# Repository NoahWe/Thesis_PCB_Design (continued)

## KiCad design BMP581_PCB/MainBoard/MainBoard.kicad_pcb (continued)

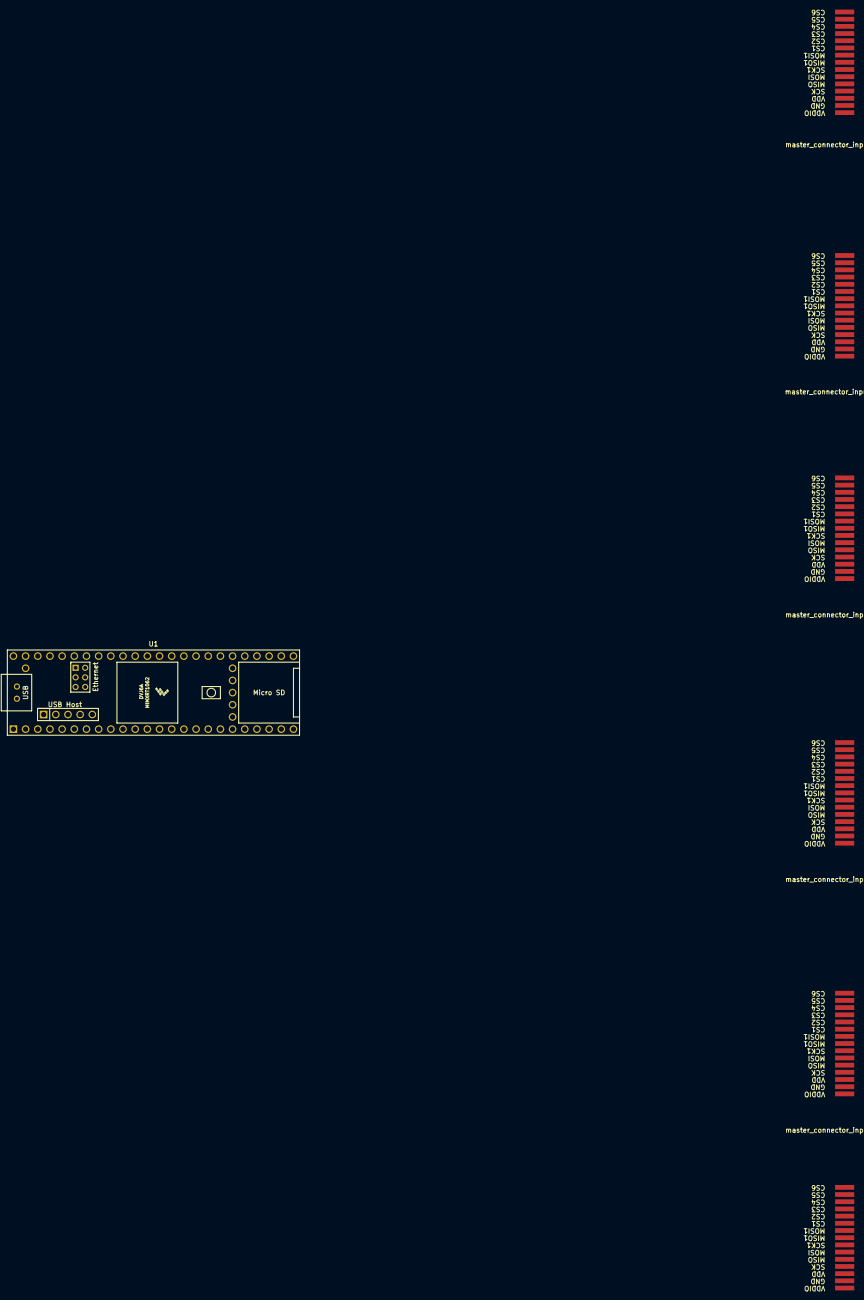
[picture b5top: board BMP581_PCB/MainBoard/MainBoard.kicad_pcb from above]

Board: 2 copper layers, 13 parts (0 on the bottom side), 42 nets.

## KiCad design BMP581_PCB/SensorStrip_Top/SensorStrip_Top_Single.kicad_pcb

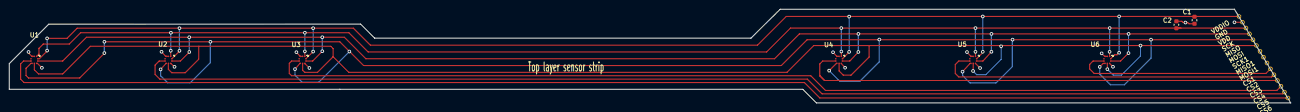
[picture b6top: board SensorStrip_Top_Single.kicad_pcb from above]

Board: 2 copper layers, 283.0 x 20.7 mm, 9 parts (0 on the bottom side), 12 nets.

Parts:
C1, C2: 470nF; C_0603_1608Metric
TopConnector1: std_master_output; Strip_pins_top
U1, U2, U3, U4, U5, U6: BMP581_Landing_Pattern

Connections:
GND: C1.1, C2.1, TopConnector1.2 (GND), U1.3 (GND), U1.8 (GND), U1.9 (GND), U2.3 (GND), U2.8 (GND), U2.9 (GND), U3.3 (GND), U3.8 (GND), U3.9 (GND), U4.3 (GND), U4.8 (GND), U4.9 (GND), U5.3 (GND), U5.8 (GND), U5.9 (GND), U6.3 (GND), U6.8 (GND), U6.9 (GND)
unnamed: TopConnector1.10 (CS1), U6.6 (CSB)
unnamed: TopConnector1.11 (CS2), U5.6 (CSB)
unnamed: TopConnector1.12 (CS3), U4.6 (CSB)
unnamed: TopConnector1.13 (CS4), U3.6 (CSB)
unnamed: TopConnector1.14 (CS5), U2.6 (CSB)
unnamed: TopConnector1.15 (CS6), U1.6 (CSB)
unnamed: TopConnector1.5 (MISO), U1.5 (SDO), U2.5 (SDO), U3.5 (SDO), U4.5 (SDO), U5.5 (SDO), U6.5 (SDO)
unnamed: TopConnector1.6 (MOSI), U1.4 (SDI), U2.4 (SDI), U3.4 (SDI), U4.4 (SDI), U5.4 (SDI), U6.4 (SDI)
unnamed: TopConnector1.4 (SCK), U1.2 (SCK), U2.2 (SCK), U3.2 (SCK), U4.2 (SCK), U5.2 (SCK), U6.2 (SCK)
unnamed: C2.2, TopConnector1.3 (VDD), U1.10 (VDD), U2.10 (VDD), U3.10 (VDD), U4.10 (VDD), U5.10 (VDD), U6.10 (VDD)
unnamed: C1.2, TopConnector1.1 (VDDIO), U1.1 (VDDIO), U2.1 (VDDIO), U3.1 (VDDIO), U4.1 (VDDIO), U5.1 (VDDIO), U6.1 (VDDIO)

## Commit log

2023-05-15 Added Teensy submodule
2023-05-17 started pcb development
2023-05-18 New footprint submodule + progress
2023-05-22 update strips
2023-05-22 removed unnecessary files
2023-06-01 Top sensor strip completed v1
2023-06-05 All PCBs v1
2023-06-06 Incorporate feedback
2023-06-06 remove backups
2023-06-06 add gitignore file
2023-06-07 update for file transfer / cleanup some traces
2023-06-08 added gerber and drill files to ignore list
2023-06-08 transfer files to laptop for order
2023-06-13 Ordered PCBs
